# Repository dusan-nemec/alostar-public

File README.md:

# APVV SK-IL-RD-0002: Advanced Localization Sensors and Techniques for Autonomous vehicles and Robots

## Anotácia
Integrácia globálnej satelitnej navigácie, odometrov a inerciálnych snímačov je štandardne používanou technikou na lokalizáciu pozemných vozidiel a mobilných robotov. Viacero štúdií naznačuje, že inerciálne snímače umiestnené na kolesách vozidla môžu zvýšiť presnosť navigačného systému. Popritom techniky hlbokého učenia boli aplikované vo viacerých navigačných úlohách, pričom vykazovali lepšie vlastnosti v porovnaní s metódami založenými na matematických modeloch. V rámci tohto projektu navrhujeme vyvinúť softvérový rámec (framework) využívajúci strojové učenie, ktorý by umožnil lepšie využiť potenciál inerciálnych snímačov umiestnených na kolesách vozidla. Budú preskúmané možnosti optimálneho umiestnenia inerciálnych snímačov a následne bude odvodený a implementovaný hybridný navigačný filter využívajúci strojové učenie. Navrhnuté algoritmy budú validované pomocou experimentov v reálnych podmienkach s využitím pozemných vozidiel a mobilných kolesových robotov.

## Štruktúra repozitáru
### models
Priečinok obsahuje softvérovú implementáciu simulačných modelov kolesových robotov. Je rozdelený na podpriečinky:
- `kinematics`- obsahuje kinematický model diferenciálne riadeného robota v jazyku MATLAB
- `dynamics` - obsahuje model dynamiky 4-kolesového šmykom riadeného robota v jazyku MATLAB
- `wheel` - obsahuje simulačný model IMU snímača namontovaného na kolese robota v jazyku Python

### pcb
Priečinok obsahuje podklady na výrobu DPS prototypu meracej jednotky. Obsahuje súbory:
- `wheel.sch` - elektrická schéma zapojenia pre EAGLE
- `wheel.brd` - rozmiestnenie komponentov pre EAGLE
- `wheel-bottom.pdf` - ukážka spodnej vrstvy DPS vo formáte PDF
- `wheel-top.pdf` - ukážka vrchnej vrstvy DPS vo formáte PDF
- `wheel-scheme.pdf` - elektrická schéma zapojenia vo formáte PDF

### firmware
Priečinok obsahuje zdrojový kód riadiaceho programu meracej jednotky navrhnutej v rámci projektu. Jednotka je vybavená riadiacim mikropočítačom typu ESP32 a je programovateľná v prostredí Arduino IDE. Obsahuje podpriečinky:
- `lib` - priečinok obsahuje custom knižnice Arduino. Pre úspešné skompilovanie firmvéru je potrebné tieto knižnice skopírovať do priečinka `~\Documents\Arduino\libraries`
- `wheel_sensor` - priečinok obsahuje projekt firmvéru v jazyku C++, otvoriteľný v prostredí Arduino IDE

### protocol
Priečinok obsahuje textový opis komunikačného protokolu meracej jednotky vo formáte PDF.

### logger
Priečinok obsahuje zdrojový kód jednoduchého softvéru na ukladanie údajov z meracích jednotiek napísaný v jazyku Python.
- `logger.py` - hlavný spustiteľný skript
- `tcp.py` - klient pre TCP/IP komunikáciu
- `udp.py` - klient pre UDP/IP komunikáciu

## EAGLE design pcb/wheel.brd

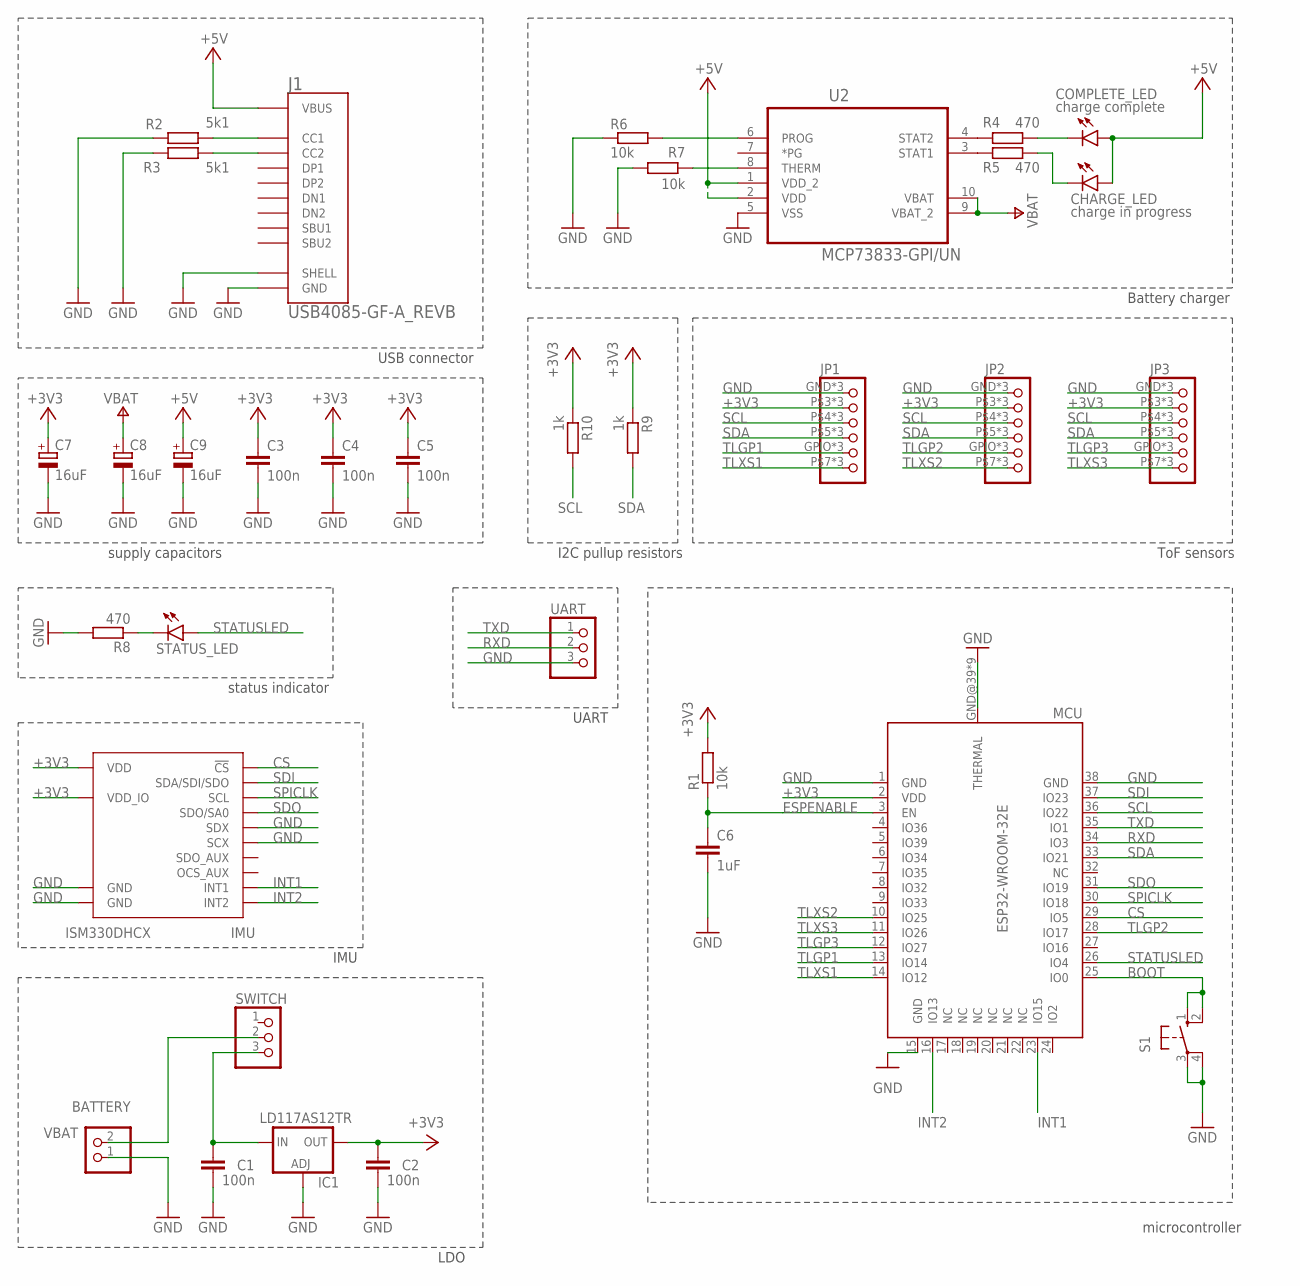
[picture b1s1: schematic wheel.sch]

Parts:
BATTERY: PINHD-1X2; 1X02
C1, C2, C3, C4, C5: 100n; C1206
C6: 1uF; C1206
C7, C8, C9: 16uF; E2,5-7
CHARGE_LED: charge in progress; CHIPLED_1206
COMPLETE_LED: charge complete; CHIPLED_1206
IC1: LD117AS12TR; SOT223
IMU: ISM330DHCX; LGA-14L
J1: USB4085-GF-A_REVB; GCT_USB4085-GF-A_REVB
JP1, JP2, JP3: PINHD-1X6; 1X06
MCU: ESP32-WROOM-32E
R1, R6, R7: 10k; R1206
R2, R3: 5k1; R1206
R4, R5, R8: 470; R1206
R9, R10: 1k; R1206
S1: 10-XX; B3F-10XX
STATUS_LED: status; CHIPLED_1206
SWITCH: PINHD-1X3; 1X03
U2: MCP73833-GPI/UN; SOP50P490X110-10N
UART: PINHD-1X3; 1X03

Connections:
+3V3: C2.1, C3.1, C4.1, C5.1, C7.+, IC1.4 (OUT), IMU.P5 (VDD_IO), IMU.P8 (VDD), JP1.P$3 (2), JP1.P$8 (2), JP1.VCC (2), JP2.P$3 (2), JP2.P$8 (2), JP2.VCC (2), JP3.P$3 (2), JP3.P$8 (2), JP3.VCC (2), MCU.2 (VDD), R1.2, R9.1, R10.1
+5V: C9.+, CHARGE_LED.A, COMPLETE_LED.A, J1.A4 (VBUS), J1.A9 (VBUS), J1.B4 (VBUS), J1.B9 (VBUS), U2.1 (VDD_2), U2.2 (VDD)
BOOT: MCU.25 (IO0), S1.1 (S), S1.2 (S1)
CS: IMU.P12 (!CS!), MCU.29 (IO5)
ESPENABLE: C6.1, MCU.3 (EN), R1.1
GND: BATTERY.1, C1.2, C2.2, C3.2, C4.2, C5.2, C6.2, C7.-, C8.-, C9.-, IC1.1 (ADJ), IMU.P2 (SDX), IMU.P3 (SCX), IMU.P6 (GND), IMU.P7 (GND), J1.A1 (GND), J1.A12 (GND), J1.B1 (GND), J1.B12 (GND), J1.S1 (SHELL), J1.S2 (SHELL), J1.S3 (SHELL), J1.S4 (SHELL), JP1.GND (1), JP1.P$1 (1), JP1.P$2 (1), JP2.GND (1), JP2.P$1 (1), JP2.P$2 (1), JP3.GND (1), JP3.P$1 (1), JP3.P$2 (1), MCU.1 (GND), MCU.15 (GND), MCU.38 (GND), MCU.GND@39 (THERMAL), MCU.GND@40 (THERMAL), MCU.GND@41 (THERMAL), MCU.GND@42 (THERMAL), MCU.GND@43 (THERMAL), MCU.GND@44 (THERMAL), MCU.GND@45 (THERMAL), MCU.GND@46 (THERMAL), MCU.GND@47 (THERMAL), R2.2, R3.2, R6.2, R7.2, R8.2, S1.3, S1.4 (P1), U2.5 (VSS), UART.3
INT1: IMU.P4 (INT1), MCU.23 (IO15)
INT2: IMU.P9 (INT2), MCU.16 (IO13)
unnamed: R4.2, U2.4 (STAT2)
unnamed: C1.1, IC1.3 (IN), SWITCH.3
unnamed: J1.A5 (CC1), R2.1
unnamed: J1.B5 (CC2), R3.1
unnamed: R5.2, U2.3 (STAT1)
unnamed: R6.1, U2.6 (PROG)
unnamed: COMPLETE_LED.C, R4.1
unnamed: CHARGE_LED.C, R5.1
unnamed: R7.1, U2.8 (THERM)
unnamed: R8.1, STATUS_LED.C
RXD: MCU.34 (IO3), UART.2
SCL: JP1.P$4 (3), JP1.P$9 (3), JP1.SCL (3), JP2.P$4 (3), JP2.P$9 (3), JP2.SCL (3), JP3.P$4 (3), JP3.P$9 (3), JP3.SCL (3), MCU.36 (IO22), R10.2
SDA: JP1.P$5 (4), JP1.P$10 (4), JP1.SDA (4), JP2.P$5 (4), JP2.P$10 (4), JP2.SDA (4), JP3.P$5 (4), JP3.P$10 (4), JP3.SDA (4), MCU.33 (IO21), R9.2
SDI: IMU.P14 (SDA/SDI/SDO), MCU.37 (IO23)
SDO: IMU.P1 (SDO/SA0), MCU.31 (IO19)
SPICLK: IMU.P13 (SCL), MCU.30 (IO18)
STATUSLED: MCU.26 (IO4), STATUS_LED.A
TLGP1: JP1.GPIO (5), JP1.P$6 (5), JP1.P$11 (5), MCU.13 (IO14)
TLGP2: JP2.GPIO (5), JP2.P$6 (5), JP2.P$11 (5), MCU.28 (IO17)
TLGP3: JP3.GPIO (5), JP3.P$6 (5), JP3.P$11 (5), MCU.12 (IO27)
TLXS1: JP1.P$7 (6), JP1.P$12 (6), JP1.XSHUT (6), MCU.14 (IO12)
TLXS2: JP2.P$7 (6), JP2.P$12 (6), JP2.XSHUT (6), MCU.10 (IO25)
TLXS3: JP3.P$7 (6), JP3.P$12 (6), JP3.XSHUT (6), MCU.11 (IO26)
TXD: MCU.35 (IO1), UART.1
VBAT: BATTERY.2, C8.+, SWITCH.2, U2.9 (VBAT_2), U2.10 (VBAT)

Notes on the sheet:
USB connector
supply capacitors
status indicator
Battery charger
ToF sensors
I2C pullup resistors
microcontroller
IMU
UART
LDO

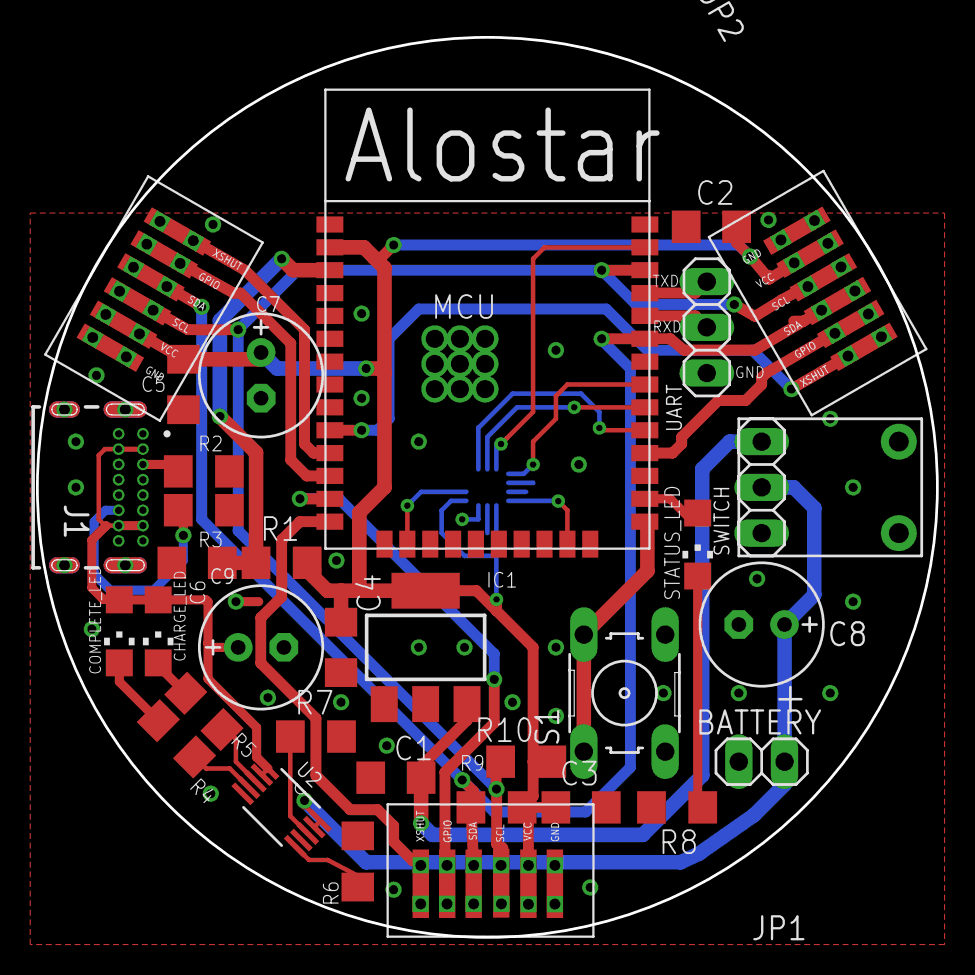
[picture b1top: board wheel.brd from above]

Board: 2 copper layers, 50.0 x 50.0 mm, 34 parts (1 on the bottom side), 33 nets.

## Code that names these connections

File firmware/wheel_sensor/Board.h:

#ifndef BOARD_H_
#define BOARD_H_

// pinout
#define LED       4
#define TLGP2     14
#define TLXS2     12
#define TLGP1     17
#define TLXS1     (-1)
#define TLGP3     27
#define TLXS3     26
#define SPI_SDI   23
#define SPI_SDO   19
#define SPI_CLK   18
#define SPI_CS    5
#define I2C_SDA   21
#define I2C_SCL   22
#define UART_RX   3
#define UART_TX   1
#define IMU_INT1  15
#define IMU_INT2  13


#endif

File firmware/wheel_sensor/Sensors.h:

#ifndef SENSORS_H_
#define SENSORS_H_

#include <Wire.h>

#include <ASM330LHHSensor.h>
#include <vl53l4cd_class.h>
#include "FIFO.h"
#include "Board.h"

// default IMU configuration
#define DEFAULT_GYRO_FS       2000    // deg/s
#define DEFAULT_ACCEL_FS      4       // g
#define DEFAULT_IMU_ODR       208.0   // Hz
#define DEFAULT_LIDAR_PERIOD  50      // ms

#define LIDAR_COUNT           3

SPIClass spi(VSPI);
ASM330LHHSensor imu(&spi, SPI_CS);
VL53L4CD lidar1(&Wire, TLXS1);
VL53L4CD lidar2(&Wire, TLXS2);
VL53L4CD lidar3(&Wire, TLXS3);
VL53L4CD* lidars[3];


int lidarInterruptPins[3] = {TLGP1, TLGP2, TLGP3};

struct Sample
{
  int64_t tim;
  float temperature;
  float gyro[3];
  float accel[3];
  float distance[3];
  float distanceErr[3];
  // TODO
};

struct SensorSettings
{
  int32_t gyroFS;
  int32_t accelFS;
  float imuODR;
  uint32_t lidarPeriod;
};

SensorSettings sensorSettings = {DEFAULT_GYRO_FS, DEFAULT_ACCEL_FS, DEFAULT_IMU_ODR, DEFAULT_LIDAR_PERIOD};
volatile bool sensorSettingsChanged = true; // sets config for the first time

Sample sample;
FIFO<Sample, 8> fifo;

int64_t getTimeMicros()
{
  struct timeval tv_now;
  gettimeofday(&tv_now, NULL);
  return (int64_t)tv_now.tv_sec * 1000000L + (int64_t)tv_now.tv_usec;
}

void initSensors()
{
  spi.begin(SPI_CLK, SPI_SDO, SPI_SDI, SPI_CS);
  pinMode(SPI_CS, OUTPUT);

  pinMode(IMU_INT1, INPUT);
  pinMode(IMU_INT2, INPUT);
  pinMode(TLGP1, INPUT_PULLUP);
  pinMode(TLGP2, INPUT_PULLUP);
  pinMode(TLGP3, INPUT_PULLUP);

  if(imu.begin() != ASM330LHH_OK)
    Serial.println("failed to init IMU.");

  imu.Set_G_FS(sensorSettings.gyroFS);
  imu.Set_X_FS(sensorSettings.accelFS);
  imu.Set_G_ODR(sensorSettings.imuODR);
  imu.Set_X_ODR(sensorSettings.imuODR);

  if(imu.Enable_X() != ASM330LHH_OK)
    Serial.println("failed to enable accel.");

  if(imu.Enable_G() != ASM330LHH_OK)
    Serial.println("failed to enable gyro.");

  if(imu.Enable_INT1(ASM330LHH_INT_DRDY_G) != ASM330LHH_OK)
    Serial.println("failed to setup INT1 pin.");

  if(imu.Enable_INT2(ASM330LHH_INT_DRDY_XL) != ASM330LHH_OK)
    Serial.println("failed to setup INT2 pin.");

  imu.Get_G_FS(&sensorSettings.gyroFS);
  imu.Get_X_FS(&sensorSettings.accelFS);
  imu.Get_X_ODR(&sensorSettings.imuODR);

  Wire.begin();

  // begin() will power-off lidar
  lidar1.begin();
  lidar2.begin();
  lidar3.begin();

  lidars[0] = &lidar1;
  lidars[1] = &lidar2;
  lidars[2] = &lidar3;

  for(int i=0; i < LIDAR_COUNT; i++)
  {
    VL53L4CD* lid = lidars[i];
    lid->InitSensor(0x55 + i);
    lid->VL53L4CD_SetRangeTiming(sensorSettings.lidarPeriod, 0); // 200 Hz
    lid->VL53L4CD_StartRanging();
  }
}

// task for reading sensors
void runSensors(void* args)
{
  while(true)
  {
    if(sensorSettingsChanged)
    {
      initSensors();
      sensorSettingsChanged = false;
    }

    for(int i=0; i < LIDAR_COUNT; i++)
    {
      if(!digitalRead(lidarInterruptPins[i]))
      {
        VL53L4CD_Result_t res;
        VL53L4CD* lid = lidars[i];
        lid->VL53L4CD_ClearInterrupt();
        if(lid->VL53L4CD_GetResult(&res) == VL53L4CD_ERROR_NONE)
        {
          if(res.range_status == 0)
          {
            // data valid
            sample.distance[i] = (float)res.distance_mm;
            sample.distanceErr[i] = (float)res.sigma_mm;
          }
          else
          {
            // data invalid
            sample.distance[i] = 0;
            sample.distanceErr[i] = 0;
          }
        }
      }
    }

    if(digitalRead(IMU_INT2))
    {
      // accelerometer ready
      imu.Get_X_Axes(sample.accel);
    }

    if(digitalRead(IMU_INT1))
    {
      // gyroscope ready, finish sample
      sample.tim = getTimeMicros();
      imu.Get_G_Axes(sample.gyro);
      imu.Get_T(&sample.temperature);

      if(sample.tim > 1000000000000000UL) // about year 2001, wait for NTP sync
        fifo.push(sample);
    }

    taskYIELD();
  }
}

#endif

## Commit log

2025-01-14 adding content
2026-01-16 + pcb/v2 + fusion implementation

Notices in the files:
parts and their libraries:
SparkFun-Sensors: Licensing: Creative Commons ShareAlike 4.0 International - https://creativecommons.org/licenses/by-sa/4.0
